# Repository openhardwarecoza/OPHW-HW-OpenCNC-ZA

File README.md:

# OPHW-HW-OpenCNC-ZA

Release link for Version 2: https://plus.google.com/+PetervanderWalt/posts/GEEHTLkx1Rs

Youtube Playlist: (Mostly the older V1 videos): https://www.youtube.com/watch?v=i0t9h2HhJ-g&list=PL1JTb6-HQgOwBOFXhe4r-cTgKN7O4TTUV
(Note: The V2 is a much more rigit beast than the V1 was - switching to OpenBuilds V-Slot made a massive difference over 12mm stainless shafts that V1 used)

Photos of the machines: https://github.com/openhardwarecoza/OPHW-HW-OpenCNC-ZA/tree/master/Photos

###Groupbuy of V2 Frames 

(March 2016:  $300 if we get 10 people): https://plus.google.com/112804366993013346159/posts/UJpufFbkruB

## New Version: V2
OPHW-HW-OpenCNC-SMW

## Legacy Version:  V1
OPHW-HW-OpenCNC-ZA

74 x Photos build Album of V1: https://plus.google.com/+PetervanderWalt/posts/8sR3STWhrXN

Specs V1: 200x300mm work area, 12mm ballscrews all round, 12mm stainless steel shafts,

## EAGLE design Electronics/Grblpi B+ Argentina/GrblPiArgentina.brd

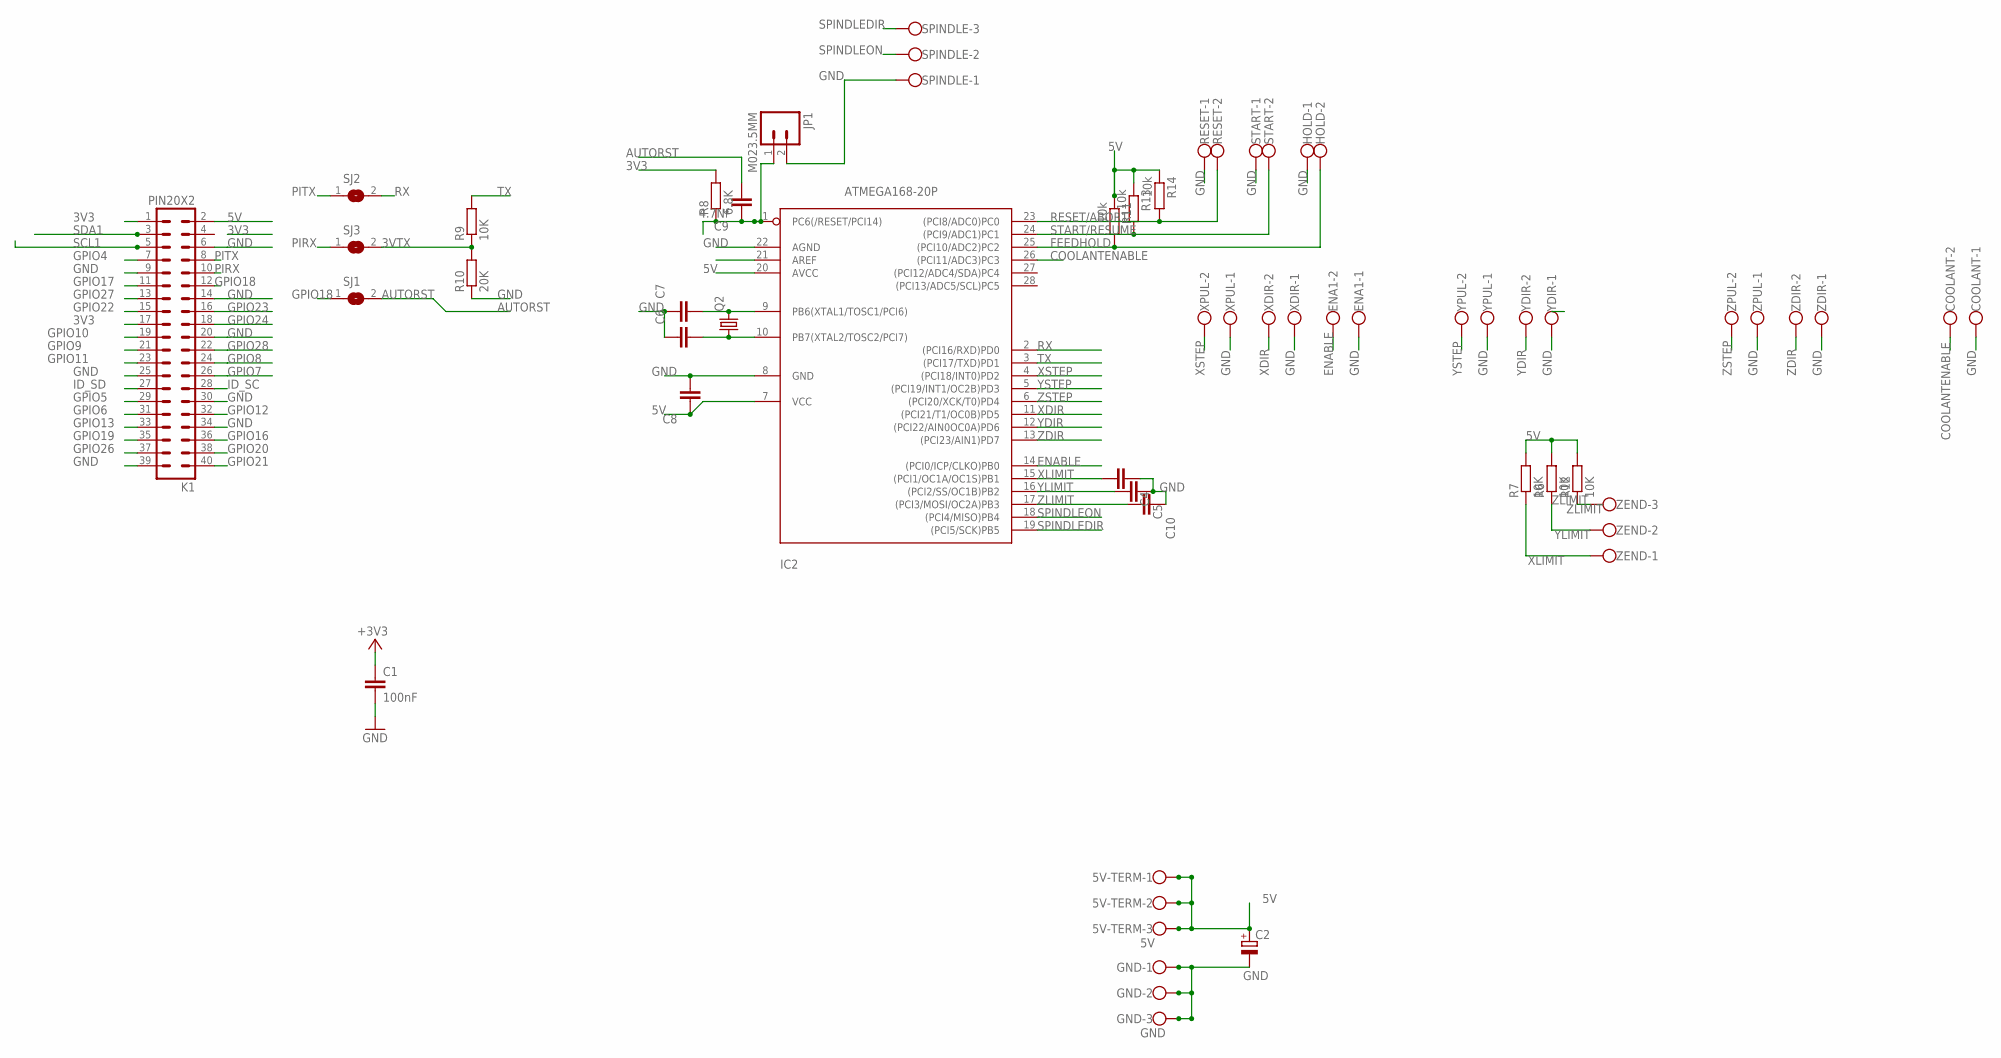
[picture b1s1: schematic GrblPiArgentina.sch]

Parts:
5V-TERM: 5V; W237-103
C1: 100nF; C025-024X044
C2: CPOL-EUE2,5-6E; E2,5-6E
C4, C5, C6, C7, C8, C10: CAPACITOR_NPOL-PTH_0.1"; C0.1PTH
C9: 4.7Nf; C0.1PTH
COOLANT: W237-102
ENA1: W237-102
GND: GND; W237-103
HOLD: W237-102
IC2: ATMEGA168-20P; DIL28-3
JP1: M023.5MM; SCREWTERMINAL-3.5MM-2
K1: PIN20X2; PIN_20X2
Q2: CRYSTALHC49U70; HC49U70
R6, R7, R9, R12: 10K; 0204/7
R8: 6.8K; 0204/7
R10: 20K; 0204/7
R11, R13, R14: 10k; 0204/7
RESET: W237-102
SJ1, SJ2, SJ3: SJ
SPINDLE: W237-103
START: W237-102
XDIR: W237-102
XPUL: W237-102
YDIR: W237-102
YPUL: W237-102
ZDIR: W237-102
ZEND: W237-103
ZPUL: W237-102

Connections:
3V3: C1.1, K1.1, K1.17, R8.2
3VTX: R9.1, R10.2, SJ3.2
5V: 5V-TERM.1, 5V-TERM.2, 5V-TERM.3, C2.+, C8.1, IC2.7 (VCC), IC2.20 (AVCC), K1.2, R6.2, R7.2, R11.1, R12.2, R13.1, R14.1
AUTORST: C9.2, SJ1.2
COOLANTENABLE: COOLANT.2, IC2.26 ((PCI11/ADC3)PC3)
ENABLE: ENA1.2, IC2.14 ((PCI0/ICP/CLKO)PB0)
FEEDHOLD: HOLD.2, IC2.25 ((PCI10/ADC2)PC2), R11.2
GND: C1.2, C2.-, C4.1, C5.1, C6.1, C7.1, C8.2, C10.1, COOLANT.1, ENA1.1, GND.1, GND.2, GND.3, HOLD.1, IC2.8 (GND), IC2.22 (AGND), JP1.2, K1.6, K1.9, K1.14, K1.20, K1.25, K1.30, K1.34, K1.39, R10.1, RESET.1, SPINDLE.1, START.1, XDIR.1, XPUL.1, YDIR.1, YPUL.1, ZDIR.1, ZPUL.1
GPIO4: K1.7
GPIO5: K1.29
GPIO6: K1.31
GPIO7: K1.26
GPIO8: K1.24
GPIO9: K1.21
GPIO10: K1.19
GPIO11: K1.23
GPIO12: K1.32
GPIO13: K1.33
GPIO16: K1.36
GPIO17: K1.11
GPIO18: K1.12, SJ1.1
GPIO19: K1.35
GPIO20: K1.38
GPIO21: K1.40
GPIO22: K1.15
GPIO23: K1.16
GPIO24: K1.18
GPIO26: K1.37
GPIO27: K1.13
GPIO28: K1.22
ID_SC: K1.28
ID_SD: K1.27
MCURESET1: C9.1, IC2.1 (PC6(/RESET/PCI14)), JP1.1, R8.1
PIRX: K1.10, SJ3.1
PITX: K1.8, SJ2.1
RESET/ABORT: IC2.23 ((PCI8/ADC0)PC0), R14.2, RESET.2
RX: IC2.2 ((PCI16/RXD)PD0), SJ2.2
SCL1: K1.5
SDA1: K1.3
SPINDLEDIR: IC2.19 ((PCI5/SCK)PB5), SPINDLE.3
SPINDLEON: IC2.18 ((PCI4/MISO)PB4), SPINDLE.2
START/RESUME: IC2.24 ((PCI9/ADC1)PC1), R13.2, START.2
TX: IC2.3 ((PCI17/TXD)PD1), R9.2
XDIR: IC2.11 ((PCI21/T1/OC0B)PD5), XDIR.2
XLIMIT: C4.2, IC2.15 ((PCI1/OC1A/OC1S)PB1), R7.1, ZEND.1
XSTEP: IC2.4 ((PCI18/INT0)PD2), XPUL.2
XTAL3: C6.2, IC2.10 (PB7(XTAL2/TOSC2/PCI7)), Q2.1
XTAL4: C7.2, IC2.9 (PB6(XTAL1/TOSC1/PCI6)), Q2.2
YDIR: IC2.12 ((PCI22/AIN0OC0A)PD6), YDIR.2
YLIMIT: C5.2, IC2.16 ((PCI2/SS/OC1B)PB2), R6.1, ZEND.2
YSTEP: IC2.5 ((PCI19/INT1/OC2B)PD3), YPUL.2
ZDIR: IC2.13 ((PCI23/AIN1)PD7), ZDIR.2
ZLIMIT: C10.2, IC2.17 ((PCI3/MOSI/OC2A)PB3), R12.1, ZEND.3
ZSTEP: IC2.6 ((PCI20/XCK/T0)PD4), ZPUL.2

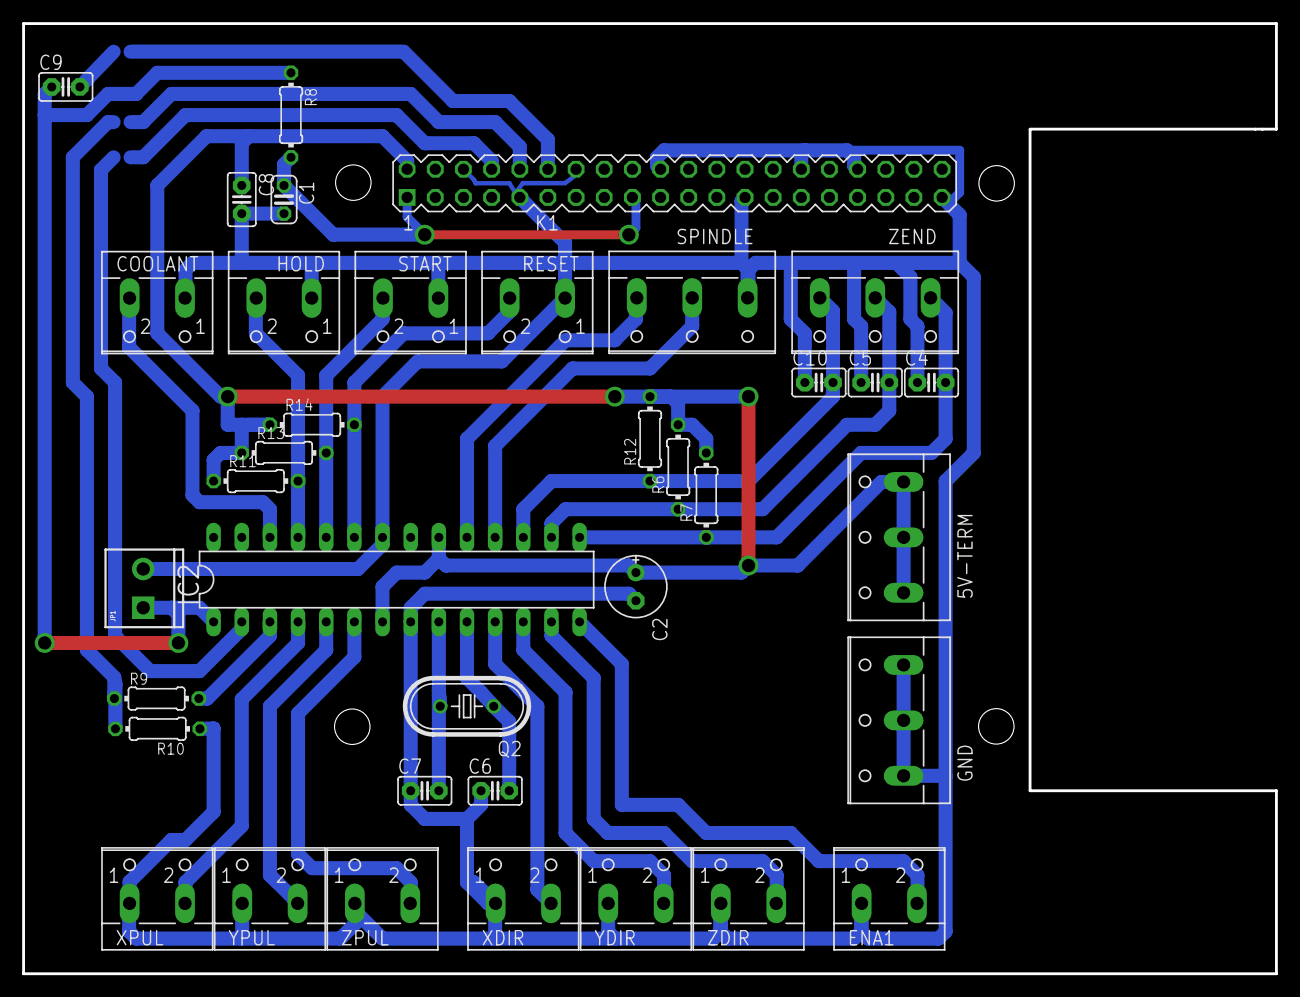
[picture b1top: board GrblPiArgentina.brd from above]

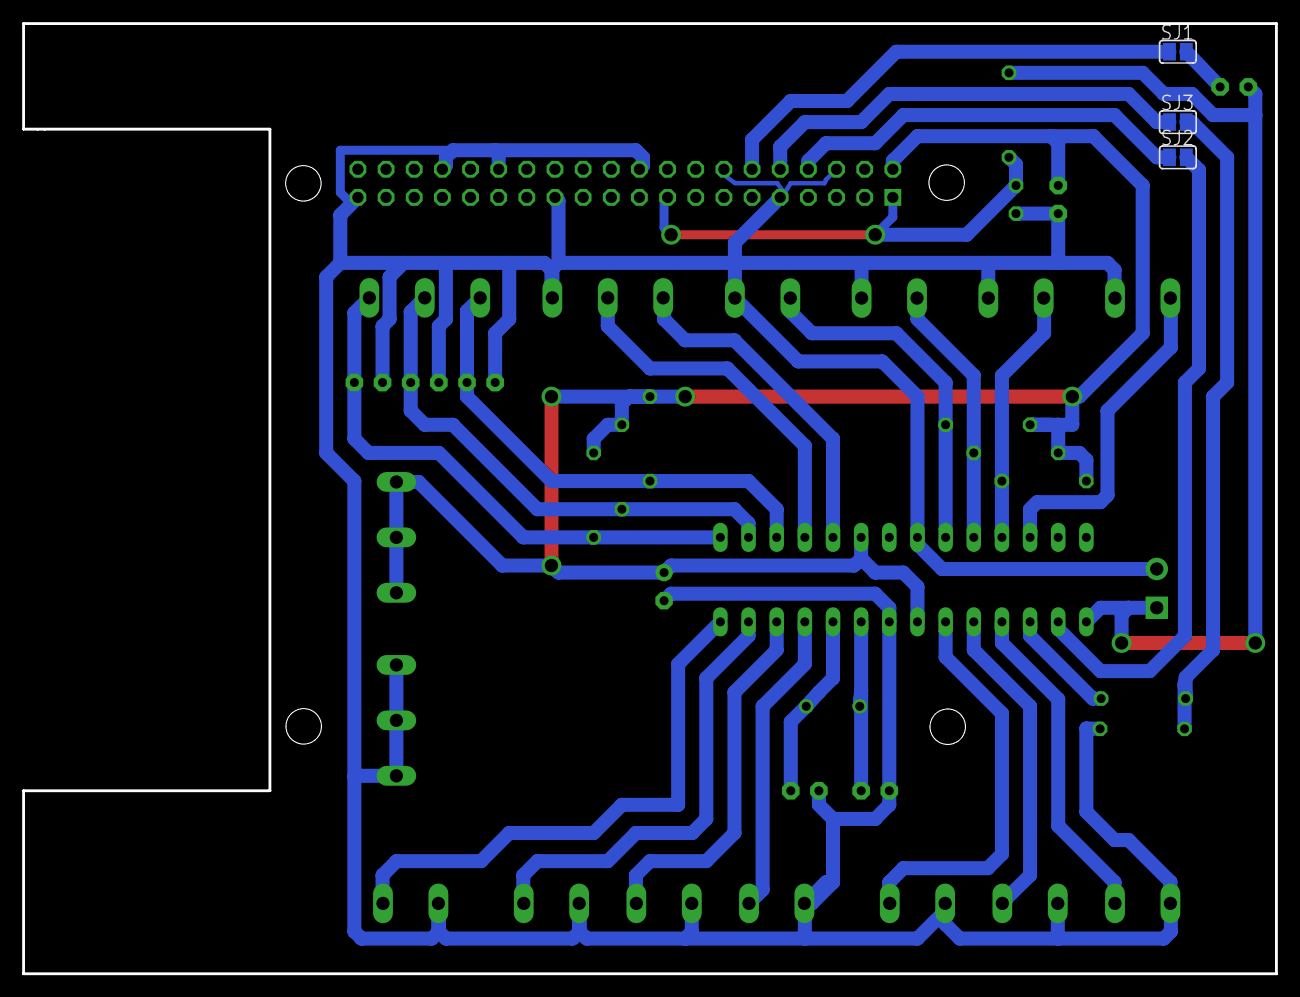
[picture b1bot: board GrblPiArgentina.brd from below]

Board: 2 copper layers, 113.0 x 85.7 mm, 40 parts (3 on the bottom side), 29 nets.

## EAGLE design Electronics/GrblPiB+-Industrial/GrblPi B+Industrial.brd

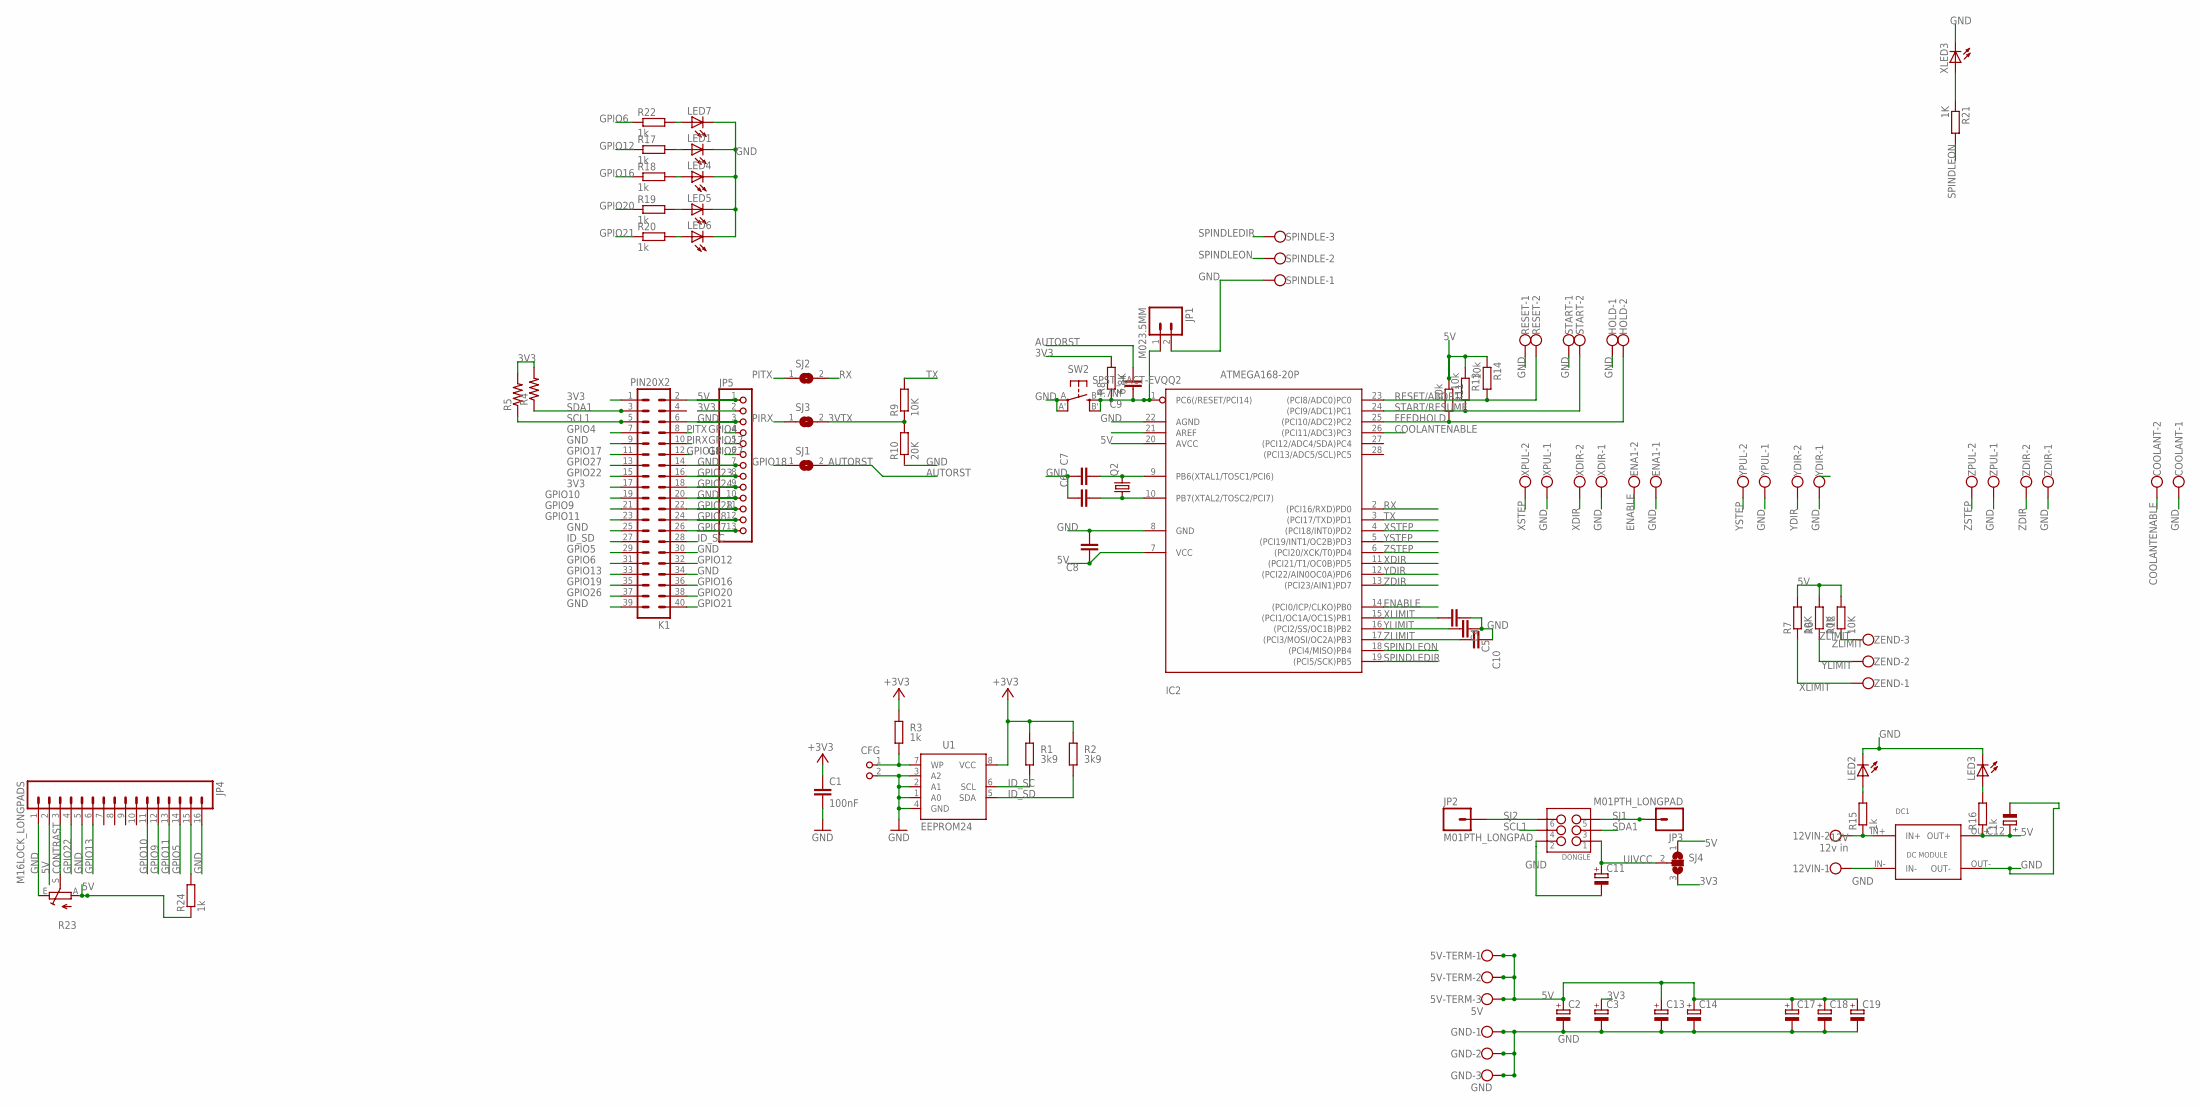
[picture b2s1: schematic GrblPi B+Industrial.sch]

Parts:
5V-TERM: 5V; W237-103
12VIN: 12v in; W237-102
C1: 100nF; C1206
C2, C3, C11, C12, C13, C14, C17, C18, C19: CPOL-EU153CLV-0405; 153CLV-0405
C4, C5, C6, C7, C8, C10: CAPACITOR_NPOL-1206; C1206
C9: 4.7Nf; C1206
CFG: PIN2_100; PIN_W_2
COOLANT: W237-102
DC1: BUCKBOOST
DONGLE: M03X2SHROUD; 2X3-SHROUDED
ENA1: W237-102
GND: GND; W237-103
HOLD: W237-102
IC2: ATMEGA168-20P; DIL28-3
JP1: M023.5MM; SCREWTERMINAL-3.5MM-2
JP2, JP3: M01PTH_LONGPAD; 1X01_LONGPAD
JP4: M16LOCK_LONGPADS; 1X16_LOCK_LONGPADS
JP5: PINHD-1X13; 1X13
K1: PIN20X2; PIN_20X2
LED1, LED2, LED3, LED4, LED5, LED6, LED7: LED5MM
Q2: CRYSTALHC49UP; HC49UP
R1, R2: 3k9; M1206; TOLERANCE 5%
R3: 1k; M1206; TOLERANCE 5%
R4, R5: R-US_M1206; M1206
R6, R7, R9, R12: 10K; R1206
R8: 6.8K; R1206
R10: 20K; R1206
R11, R13, R14: 10k; R1206
R15, R16, R17, R18, R19, R20, R22, R24: 1k; R1206
R21: 1K; R1206
R23: TRIM_EU-CA6V; CA6V
RESET: W237-102
SJ1, SJ2, SJ3: SJ
SJ4: SJ2W; SJ_2
SPINDLE: W237-103
START: W237-102
SW2: SPST_TACT-EVQQ2; EVQ-Q2
U1: EEPROM24; SOIC8
XDIR: W237-102
XLED3: LEDCHIPLED_1206; CHIPLED_1206
XPUL: W237-102
YDIR: W237-102
YPUL: W237-102
ZDIR: W237-102
ZEND: W237-103
ZPUL: W237-102

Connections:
3V3: C3.+, JP5.2, K1.1, K1.17, R4.2, R5.2, R8.2, SJ4.3
3VTX: R9.1, R10.2, SJ3.2
5V: 5V-TERM.1, 5V-TERM.2, 5V-TERM.3, C2.+, C8.1, C12.+, C13.+, C14.+, C17.+, C18.+, C19.+, DC1.OU+ (OUT+), IC2.7 (VCC), IC2.20 (AVCC), JP4.2, JP5.1, K1.2, R6.2, R7.2, R11.1, R12.2, R13.1, R14.1, R16.1, R23.A, R24.1, SJ4.1
12V: 12VIN.2, DC1.IN+, R15.1
+3V3: C1.1, R1.2, R2.2, R3.2, U1.8 (VCC)
AUTORST: C9.2, SJ1.2
CONTRAST: JP4.3, R23.S
COOLANTENABLE: COOLANT.2, IC2.26 ((PCI11/ADC3)PC3)
ENABLE: ENA1.2, IC2.14 ((PCI0/ICP/CLKO)PB0)
FEEDHOLD: HOLD.2, IC2.25 ((PCI10/ADC2)PC2), R11.2
GND: 12VIN.1, C1.2, C2.-, C3.-, C4.1, C5.1, C6.1, C7.1, C8.2, C10.1, C11.-, C12.-, C13.-, C14.-, C17.-, C18.-, C19.-, CFG.2, COOLANT.1, DC1.IN-, DC1.OUT-, DONGLE.2, ENA1.1, GND.1, GND.2, GND.3, HOLD.1, IC2.8 (GND), IC2.22 (AGND), JP1.2, JP4.1, JP4.5, JP4.16, JP5.3, JP5.7, JP5.10, K1.6, K1.9, K1.14, K1.20, K1.25, K1.30, K1.34, K1.39, LED1.K (C), LED2.K (C), LED3.K (C), LED4.K (C), LED5.K (C), LED6.K (C), LED7.K (C), R10.1, R23.E, RESET.1, SPINDLE.1, START.1, SW2.A, SW2.A' (P1), U1.1 (A0), U1.2 (A1), U1.3 (A2), U1.4 (GND), XDIR.1, XLED3.C, XPUL.1, YDIR.1, YPUL.1, ZDIR.1, ZPUL.1
GPIO4: JP5.4, K1.7
GPIO5: JP4.14, K1.29
GPIO6: K1.31, R22.1
GPIO7: JP5.13, K1.26
GPIO8: JP5.12, K1.24
GPIO9: JP4.12, K1.21
GPIO10: JP4.11, K1.19
GPIO11: JP4.13, K1.23
GPIO12: K1.32, R17.1
GPIO13: JP4.6, K1.33
GPIO16: K1.36, R18.1
GPIO17: JP5.5, K1.11
GPIO18: K1.12, SJ1.1
GPIO19: K1.35
GPIO20: K1.38, R19.1
GPIO21: K1.40, R20.1
GPIO22: JP4.4, K1.15
GPIO23: JP5.8, K1.16
GPIO24: JP5.9, K1.18
GPIO26: K1.37
GPIO27: JP5.6, K1.13
GPIO28: JP5.11, K1.22
ID_SC: K1.28, R1.1, U1.6 (SCL)
ID_SD: K1.27, R2.1, U1.5 (SDA)
LED: JP4.15, R24.2
MCURESET1: C9.1, IC2.1 (PC6(/RESET/PCI14)), JP1.1, R8.1, SW2.B (S), SW2.B' (S1)
unnamed: CFG.1, R3.1, U1.7 (WP)
unnamed: LED2.A, R15.2
unnamed: LED3.A, R16.2
unnamed: LED1.A, R17.2
unnamed: LED4.A, R18.2
unnamed: LED5.A, R19.2
unnamed: LED6.A, R20.2
unnamed: LED7.A, R22.2
PIRX: K1.10, SJ3.1
PITX: K1.8, SJ2.1
RESET/ABORT: IC2.23 ((PCI8/ADC0)PC0), R14.2, RESET.2
RX: IC2.2 ((PCI16/RXD)PD0), SJ2.2
SCL1: DONGLE.4, K1.5, R5.1
SDA1: DONGLE.3, K1.3, R4.1
SJ1: DONGLE.5, JP3.1
SJ2: DONGLE.6, JP2.1
SPINDLEDIR: IC2.19 ((PCI5/SCK)PB5), SPINDLE.3
SPINDLEON: IC2.18 ((PCI4/MISO)PB4), R21.2, SPINDLE.2
START/RESUME: IC2.24 ((PCI9/ADC1)PC1), R13.2, START.2
TX: IC2.3 ((PCI17/TXD)PD1), R9.2
UIVCC: C11.+, DONGLE.1, SJ4.2
XDIR: IC2.11 ((PCI21/T1/OC0B)PD5), XDIR.2
XLIMIT: C4.2, IC2.15 ((PCI1/OC1A/OC1S)PB1), R7.1, ZEND.1
XSTEP: IC2.4 ((PCI18/INT0)PD2), XPUL.2
XTAL3: C6.2, IC2.10 (PB7(XTAL2/TOSC2/PCI7)), Q2.1
XTAL4: C7.2, IC2.9 (PB6(XTAL1/TOSC1/PCI6)), Q2.2
YDIR: IC2.12 ((PCI22/AIN0OC0A)PD6), YDIR.2
YLIMIT: C5.2, IC2.16 ((PCI2/SS/OC1B)PB2), R6.1, ZEND.2
YSTEP: IC2.5 ((PCI19/INT1/OC2B)PD3), YPUL.2
ZDIR: IC2.13 ((PCI23/AIN1)PD7), ZDIR.2
ZLED3: R21.1, XLED3.A
ZLIMIT: C10.2, IC2.17 ((PCI3/MOSI/OC2A)PB3), R12.1, ZEND.3
ZSTEP: IC2.6 ((PCI20/XCK/T0)PD4), ZPUL.2

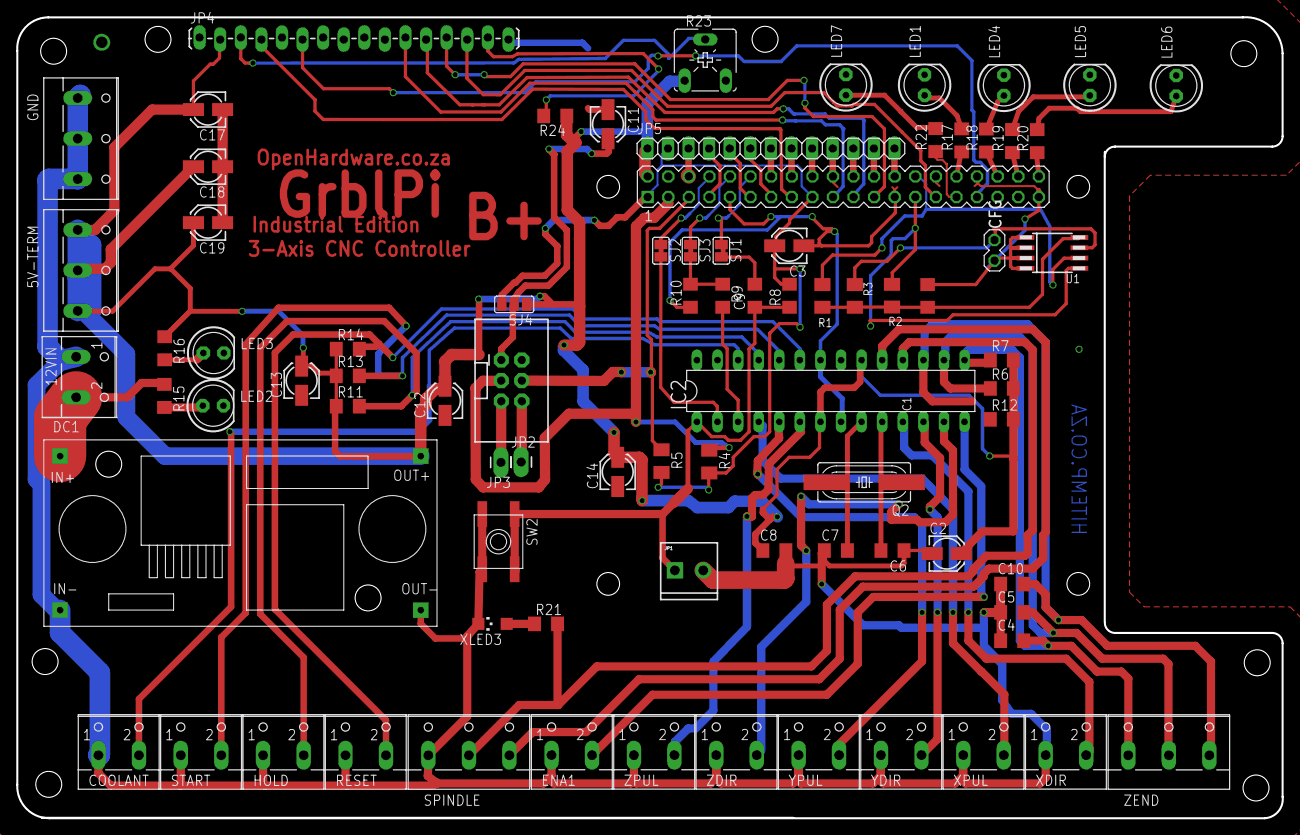
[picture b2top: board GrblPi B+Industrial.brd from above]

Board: 2 copper layers, 156.1 x 98.8 mm, 82 parts (0 on the bottom side), 68 nets.

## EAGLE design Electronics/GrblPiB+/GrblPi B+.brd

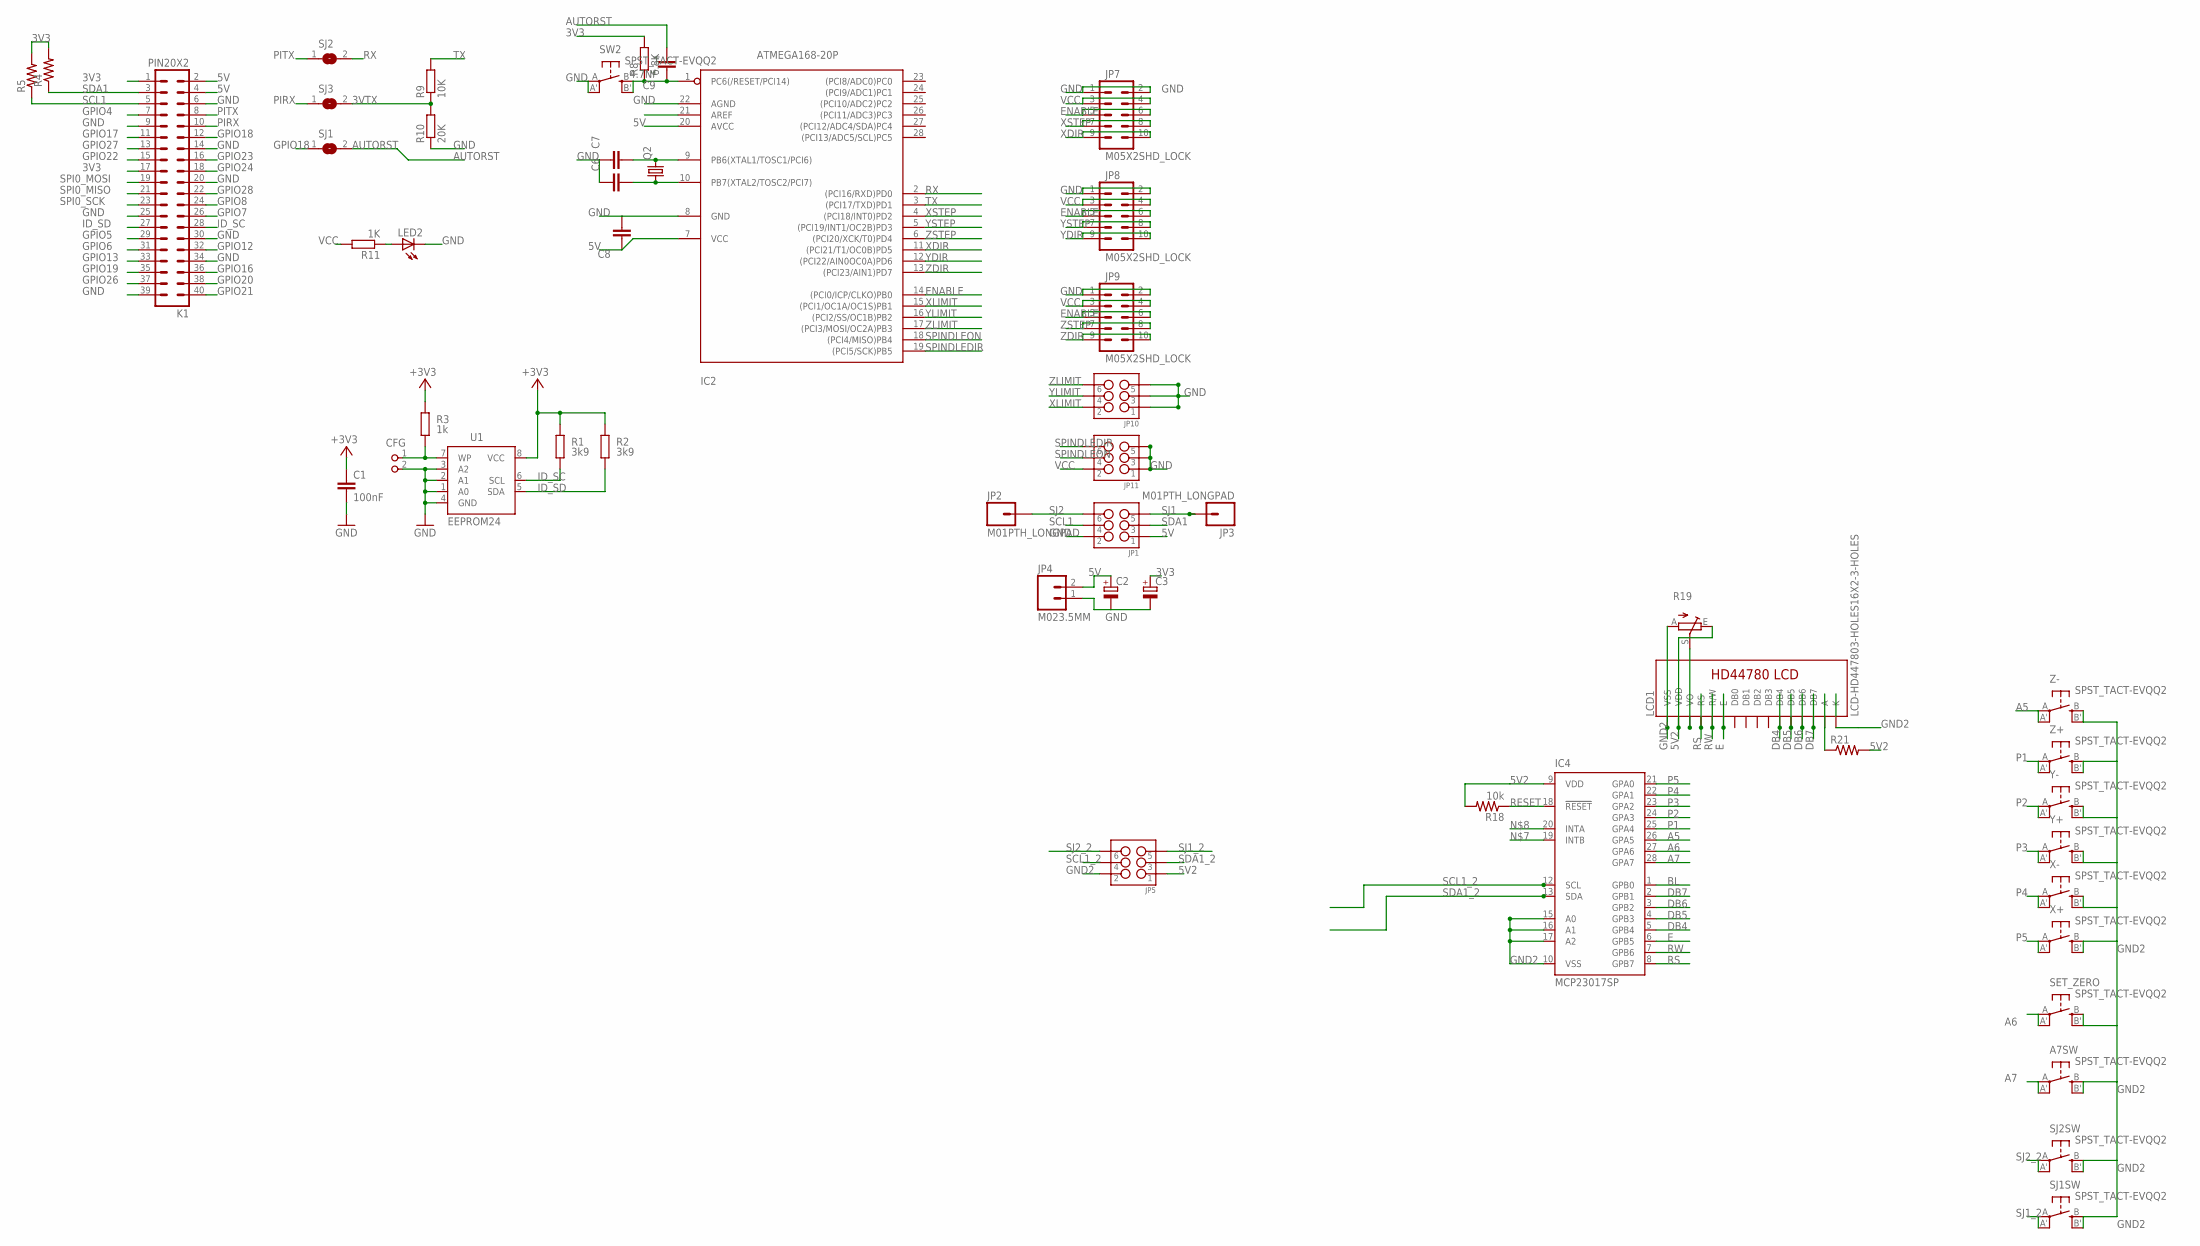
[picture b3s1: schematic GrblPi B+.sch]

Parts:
A7SW: SPST_TACT-EVQQ2; EVQ-Q2
C1: 100nF; C1206
C2, C3: CPOL-EU153CLV-0405; 153CLV-0405
C6, C7, C8: CAPACITOR_NPOL-1206; C1206
C9: 4.7Nf; C1206
CFG: PIN2_100; PIN_W_2
IC2: ATMEGA168-20P; DIL28-3
IC4: MCP23017SP; DIL28-3
JP1, JP5, JP10, JP11: M03X2SHROUD; 2X3-SHROUDED
JP2, JP3: M01PTH_LONGPAD; 1X01_LONGPAD
JP4: M023.5MM; SCREWTERMINAL-3.5MM-2
JP7, JP8, JP9: M05X2SHD_LOCK; 2X5-SHROUDED_LOCK
K1: PIN20X2; PIN_20X2
LCD1: LCD-HD447803-HOLES16X2-3-HOLES; LCD-16X2-3HOLES
LED2: LEDCHIPLED_1206; CHIPLED_1206
Q2: CRYSTALHC49UP; HC49UP
R1, R2: 3k9; M1206; TOLERANCE 5%
R3: 1k; M1206; TOLERANCE 5%
R4, R5, R21: R-US_M1206; M1206
R8: 6.8K; R1206
R9: 10K; R1206
R10: 20K; R1206
R11: 1K; R1206
R18: 10k; M1206
R19: TRIM_EU-CA6V; CA6V
SET_ZERO: SPST_TACT-EVQQ2; EVQ-Q2
SJ1, SJ2, SJ3: SJ
SJ1SW, SJ2SW: SPST_TACT-EVQQ2; EVQ-Q2
SW2: SPST_TACT-EVQQ2; EVQ-Q2
U1: EEPROM24; SOIC8
X+: SPST_TACT-EVQQ2; EVQ-Q2
X-: SPST_TACT-EVQQ2; EVQ-Q2
Y+: SPST_TACT-EVQQ2; EVQ-Q2
Y-: SPST_TACT-EVQQ2; EVQ-Q2
Z+: SPST_TACT-EVQQ2; EVQ-Q2
Z-: SPST_TACT-EVQQ2; EVQ-Q2

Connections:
3V3: C3.+, K1.1, K1.17, R4.2, R5.2, R8.2
3VTX: R9.1, R10.2, SJ3.2
5V: C2.+, C8.1, IC2.7 (VCC), IC2.20 (AVCC), JP1.1, JP4.2, K1.2, K1.4
5V2: IC4.9 (VDD), JP5.1, LCD1.2 (VDD), R18.2, R19.E, R21.2
+3V3: C1.1, R1.2, R2.2, R3.2, U1.8 (VCC)
A5: IC4.26 (GPA5), Z-.A, Z-.A' (P1)
A6: IC4.27 (GPA6), SET_ZERO.A, SET_ZERO.A' (P1)
A7: A7SW.A, A7SW.A' (P1), IC4.28 (GPA7)
AUTORST: C9.2, SJ1.2
BL: IC4.1 (GPB0)
DB4: IC4.5 (GPB4), LCD1.11 (DB4)
DB5: IC4.4 (GPB3), LCD1.12 (DB5)
DB6: IC4.3 (GPB2), LCD1.13 (DB6)
DB7: IC4.2 (GPB1), LCD1.14 (DB7)
E: IC4.6 (GPB5), LCD1.6 (E)
ENABLE: IC2.14 ((PCI0/ICP/CLKO)PB0), JP7.5, JP7.6, JP8.5, JP8.6, JP9.5, JP9.6
GND: C1.2, C2.-, C3.-, C6.1, C7.1, C8.2, CFG.2, IC2.8 (GND), IC2.22 (AGND), JP1.2, JP4.1, JP7.1, JP7.2, JP8.1, JP8.2, JP9.1, JP9.2, JP10.1, JP10.3, JP10.5, JP11.1, JP11.3, JP11.5, K1.6, K1.9, K1.14, K1.20, K1.25, K1.30, K1.34, K1.39, LED2.C, R10.1, SW2.A, SW2.A' (P1), U1.1 (A0), U1.2 (A1), U1.3 (A2), U1.4 (GND)
GND2: A7SW.B (S), A7SW.B' (S1), IC4.10 (VSS), IC4.15 (A0), IC4.16 (A1), IC4.17 (A2), JP5.2, LCD1.1 (VSS), LCD1.16 (K), R19.A, SET_ZERO.B (S), SET_ZERO.B' (S1), SJ1SW.B (S), SJ1SW.B' (S1), SJ2SW.B (S), SJ2SW.B' (S1), X+.B (S), X+.B' (S1), X-.B (S), X-.B' (S1), Y+.B (S), Y+.B' (S1), Y-.B (S), Y-.B' (S1), Z+.B (S), Z+.B' (S1), Z-.B (S), Z-.B' (S1)
GPIO4: K1.7
GPIO5: K1.29
GPIO6: K1.31
GPIO7: K1.26
GPIO8: K1.24
GPIO12: K1.32
GPIO13: K1.33
GPIO16: K1.36
GPIO17: K1.11
GPIO18: K1.12, SJ1.1
GPIO19: K1.35
GPIO20: K1.38
GPIO21: K1.40
GPIO22: K1.15
GPIO23: K1.16
GPIO24: K1.18
GPIO26: K1.37
GPIO27: K1.13
GPIO28: K1.22
ID_SC: K1.28, R1.1, U1.6 (SCL)
ID_SD: K1.27, R2.1, U1.5 (SDA)
MCURESET1: C9.1, IC2.1 (PC6(/RESET/PCI14)), R8.1, SW2.B (S), SW2.B' (S1)
unnamed: CFG.1, R3.1, U1.7 (WP)
unnamed: LCD1.3 (VO), R19.S
unnamed: LCD1.15 (A), R21.1
unnamed: LED2.A, R11.1
P1: IC4.25 (GPA4), Z+.A, Z+.A' (P1)
P2: IC4.24 (GPA3), Y-.A, Y-.A' (P1)
P3: IC4.23 (GPA2), Y+.A, Y+.A' (P1)
P4: IC4.22 (GPA1), X-.A, X-.A' (P1)
P5: IC4.21 (GPA0), X+.A, X+.A' (P1)
PIRX: K1.10, SJ3.1
PITX: K1.8, SJ2.1
RESET: IC4.18 (!RESET), R18.1
RS: IC4.8 (GPB7), LCD1.4 (RS)
RW: IC4.7 (GPB6), LCD1.5 (R/W)
RX: IC2.2 ((PCI16/RXD)PD0), SJ2.2
SCL1: JP1.4, K1.5, R5.1
SCL1_2: IC4.12 (SCL), JP5.4
SDA1: JP1.3, K1.3, R4.1
SDA1_2: IC4.13 (SDA), JP5.3
SJ1: JP1.5, JP3.1
SJ1_2: JP5.5, SJ1SW.A, SJ1SW.A' (P1)
SJ2: JP1.6, JP2.1
SJ2_2: JP5.6, SJ2SW.A, SJ2SW.A' (P1)
SPI0_MISO: K1.21
SPI0_MOSI: K1.19
SPI0_SCK: K1.23
SPINDLEDIR: IC2.19 ((PCI5/SCK)PB5), JP11.6
SPINDLEON: IC2.18 ((PCI4/MISO)PB4), JP11.4
TX: IC2.3 ((PCI17/TXD)PD1), R9.2
VCC: JP7.3, JP7.4, JP8.3, JP8.4, JP9.3, JP9.4, JP11.2, R11.2
XDIR: IC2.11 ((PCI21/T1/OC0B)PD5), JP7.9, JP7.10
XLIMIT: IC2.15 ((PCI1/OC1A/OC1S)PB1), JP10.2
XSTEP: IC2.4 ((PCI18/INT0)PD2), JP7.7, JP7.8
XTAL3: C6.2, IC2.10 (PB7(XTAL2/TOSC2/PCI7)), Q2.1
XTAL4: C7.2, IC2.9 (PB6(XTAL1/TOSC1/PCI6)), Q2.2
YDIR: IC2.12 ((PCI22/AIN0OC0A)PD6), JP8.9, JP8.10
YLIMIT: IC2.16 ((PCI2/SS/OC1B)PB2), JP10.4
YSTEP: IC2.5 ((PCI19/INT1/OC2B)PD3), JP8.7, JP8.8
ZDIR: IC2.13 ((PCI23/AIN1)PD7), JP9.9, JP9.10
ZLIMIT: IC2.17 ((PCI3/MOSI/OC2A)PB3), JP10.6
ZSTEP: IC2.6 ((PCI20/XCK/T0)PD4), JP9.7, JP9.8

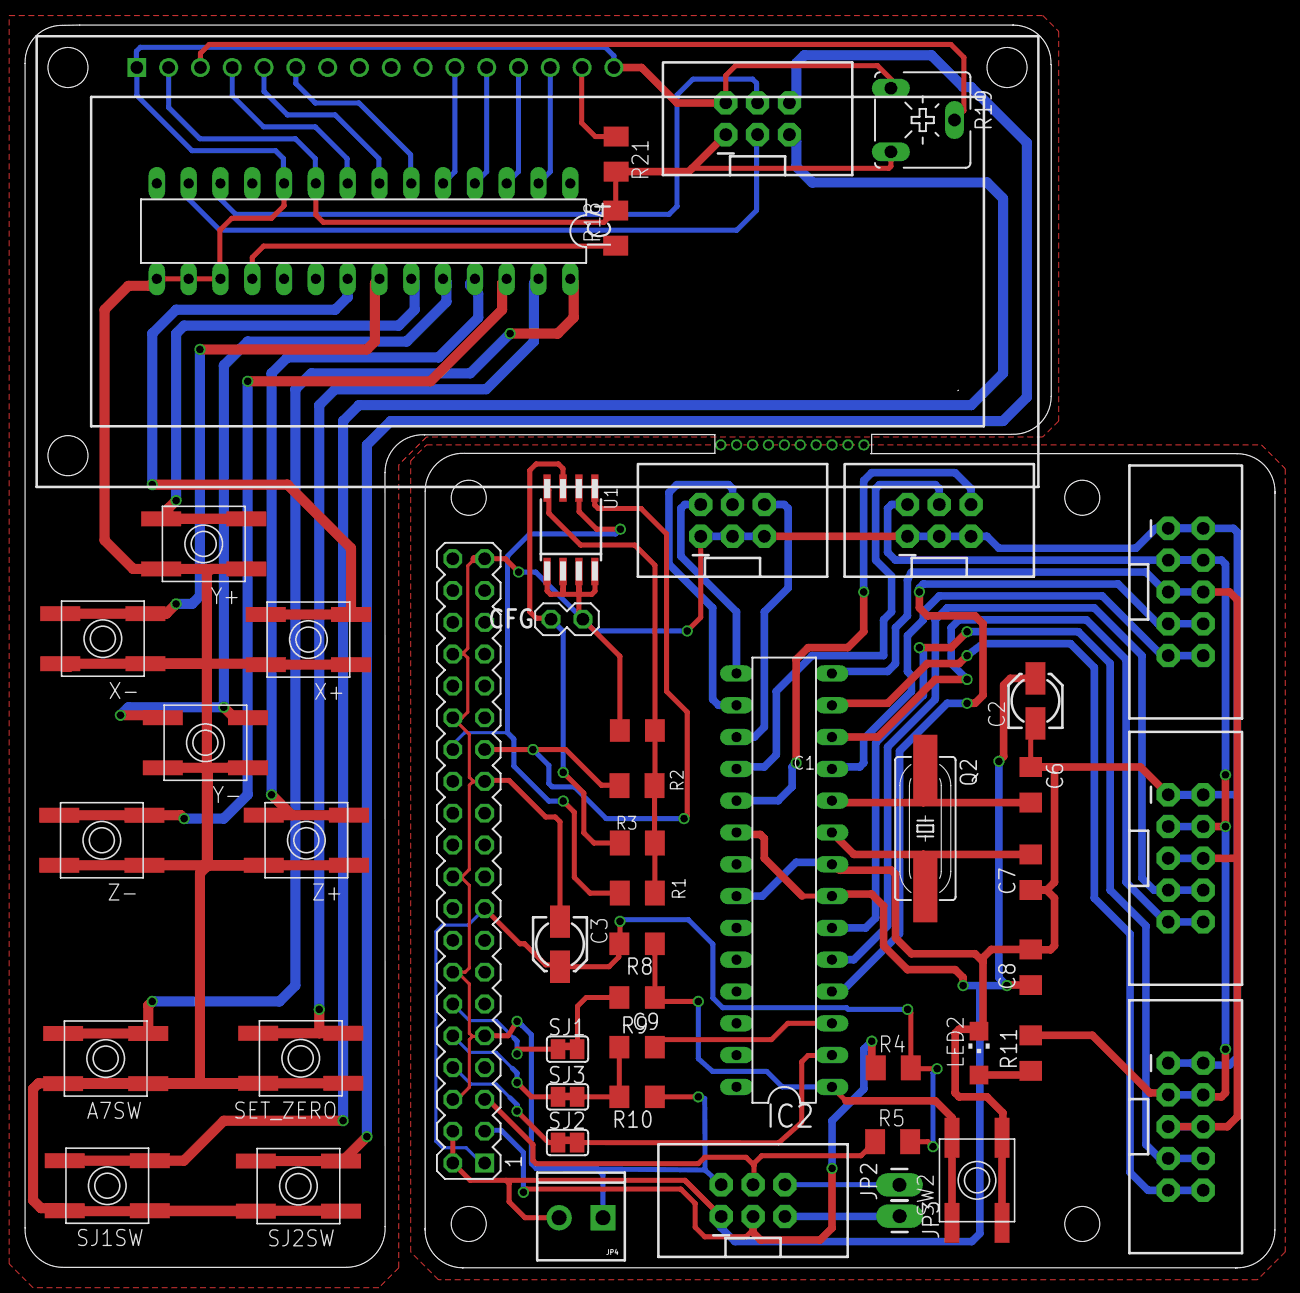
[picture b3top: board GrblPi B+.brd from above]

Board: 2 copper layers, 99.8 x 99.3 mm, 51 parts (0 on the bottom side), 59 nets.

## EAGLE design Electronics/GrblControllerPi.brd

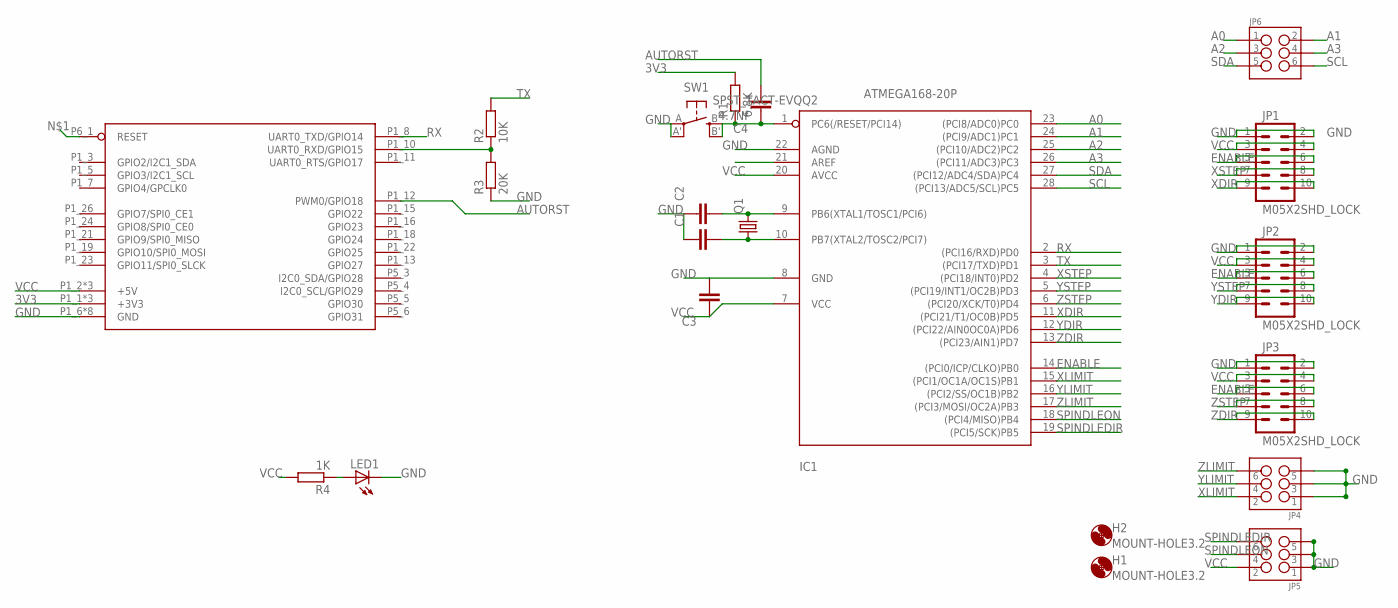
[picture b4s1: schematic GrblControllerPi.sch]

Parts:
C1, C2, C3: CAPACITOR_NPOL-1206; C1206
C4: 4.7Nf; C1206
H1, H2: MOUNT-HOLE3.2; 3,2
IC1: ATMEGA168-20P; DIL28-3
JP1, JP2, JP3: M05X2SHD_LOCK; 2X5-SHROUDED_LOCK
JP4, JP5, JP6: M03X2SHROUD; 2X3-SHROUDED
LED1: LEDCHIPLED_1206; CHIPLED_1206
Q1: CRYSTALHC49UP; HC49UP
R1: 6.8K; R1206
R2: 10K; R1206
R3: 20K; R1206
R4: 1K; R1206
SW1: SPST_TACT-EVQQ2; EVQ-Q2
U$1: RPI-B-V2SHIELD; RPI-B-V2-SHIELD

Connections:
3V3: R1.2, U$1.P1_1 (+3V3), U$1.P1_17 (+3V3), U$1.P5_2 (+3V3)
A0: IC1.23 ((PCI8/ADC0)PC0), JP6.1
A1: IC1.24 ((PCI9/ADC1)PC1), JP6.2
A2: IC1.25 ((PCI10/ADC2)PC2), JP6.3
A3: IC1.26 ((PCI11/ADC3)PC3), JP6.4
AUTORST: C4.2, U$1.P1_12 (PWM0/GPIO18)
ENABLE: IC1.14 ((PCI0/ICP/CLKO)PB0), JP1.5, JP1.6, JP2.5, JP2.6, JP3.5, JP3.6
GND: C1.1, C2.1, C3.2, IC1.8 (GND), IC1.22 (AGND), JP1.1, JP1.2, JP2.1, JP2.2, JP3.1, JP3.2, JP4.1, JP4.3, JP4.5, JP5.1, JP5.3, JP5.5, LED1.C, R3.1, SW1.A, SW1.A' (P1), U$1.P1_6 (GND), U$1.P1_9 (GND), U$1.P1_14 (GND), U$1.P1_20 (GND), U$1.P1_25 (GND), U$1.P5_7 (GND), U$1.P5_8 (GND), U$1.P6_2 (GND)
GPIO30: U$1.P5_5 (GPIO30)
GPIO31: U$1.P5_6 (GPIO31)
I2C0_SCL/GPIO29: U$1.P5_4 (I2C0_SCL/GPIO29)
I2C0_SDA/GPIO28: U$1.P5_3 (I2C0_SDA/GPIO28)
MCURESET: C4.1, IC1.1 (PC6(/RESET/PCI14)), R1.1, SW1.B (S), SW1.B' (S1)
unnamed: LED1.A, R4.1
RX: IC1.2 ((PCI16/RXD)PD0), U$1.P1_8 (UART0_TXD/GPIO14)
SCL: IC1.28 ((PCI13/ADC5/SCL)PC5), JP6.6
SDA: IC1.27 ((PCI12/ADC4/SDA)PC4), JP6.5
SPINDLEDIR: IC1.19 ((PCI5/SCK)PB5), JP5.6
SPINDLEON: IC1.18 ((PCI4/MISO)PB4), JP5.4
TX: IC1.3 ((PCI17/TXD)PD1), R2.2
TX3V3: R2.1, R3.2, U$1.P1_10 (UART0_RXD/GPIO15)
VCC: C3.1, IC1.7 (VCC), IC1.20 (AVCC), JP1.3, JP1.4, JP2.3, JP2.4, JP3.3, JP3.4, JP5.2, R4.2, U$1.P1_2 (+5V), U$1.P1_4 (+5V), U$1.P5_1 (+5V)
XDIR: IC1.11 ((PCI21/T1/OC0B)PD5), JP1.9, JP1.10
XLIMIT: IC1.15 ((PCI1/OC1A/OC1S)PB1), JP4.2
XSTEP: IC1.4 ((PCI18/INT0)PD2), JP1.7, JP1.8
XTAL1: C2.2, IC1.9 (PB6(XTAL1/TOSC1/PCI6)), Q1.2
XTAL2: C1.2, IC1.10 (PB7(XTAL2/TOSC2/PCI7)), Q1.1
YDIR: IC1.12 ((PCI22/AIN0OC0A)PD6), JP2.9, JP2.10
YLIMIT: IC1.16 ((PCI2/SS/OC1B)PB2), JP4.4
YSTEP: IC1.5 ((PCI19/INT1/OC2B)PD3), JP2.7, JP2.8
ZDIR: IC1.13 ((PCI23/AIN1)PD7), JP3.9, JP3.10
ZLIMIT: IC1.17 ((PCI3/MOSI/OC2A)PB3), JP4.6
ZSTEP: IC1.6 ((PCI20/XCK/T0)PD4), JP3.7, JP3.8

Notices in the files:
Electronics/GrblControllerPi.brd:
CC-BY-NC
parts and their libraries:
raspberry: This library stands under the CERN Open Hardware Licence.
SparkFun-Connectors: Licensing: Creative Commons ShareAlike 4.0 International - https://creativecommons.org/licenses/by-sa/4.0
